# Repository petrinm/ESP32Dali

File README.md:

# ESP32Dali

ESP32Dali is an ESP32-based, [ESPHome](https://esphome.io/)-friendly interface to [DALI](https://en.wikipedia.org/wiki/Digital_Addressable_Lighting_Interface) lighting devices. It acts as a master on the DALI bus through an isolated front-end, and can also provide 18 V DALI supply voltage from 5 V input.

The board is a matchbox-sized 2-layer PCB that hosts an ESP32-WROOM-32 plus the DALI interface.

- Schematic & PCB: `hw/` ([KiCanvas](https://kicanvas.org/?github=https%3A%2F%2Fgithub.com%2Fpetrinm%2FESP32Dali%2Fblob%2Fmain%2Fhw%2FESPDali.kicad_sch), [PDF](https://github.com/petrinm/ESP32Dali/blob/main/hw/ESPDali.pdf))
- 3D STEP and printable enclosure: `3d/`
- ESPHome external components: `components/`

## Example ESPHome configuration

The `dali` component can be pulled in as an [external component](https://esphome.io/components/external_components), so the same configuration works on the ESP32Dali board and on any other ESP32 with a compatible DALI front-end.

```yaml
esphome:
  name: livingroom
  friendly_name: Livingroom

esp32:
  board: esp32dev
  framework:
    type: arduino

external_components:
  - source:
      type: git
      url: https://github.com/petrinm/ESP32Dali.git
    components: [ dali ]

dali:
  id: dali_if
  tx_pin:
    number: 17
    inverted: true
  rx_pin:
    number: 16
    inverted: true

light:
  # Dim-only gear on one short address:
  - platform: dali
    name: "LED strip"
    interface: dali_if
    address: 5
    default_transition_length: 1s   # converted to DALI fade time on the gear

# Dual DAPC CT (two DAPC channels, two short addresses):
# - platform: dali
#   name: "TW panel"
#   interface: dali_if
#   cold_white_address: 0
#   warm_white_address: 1
#   cold_white_color_temperature: 6536 K
#   warm_white_color_temperature: 2000 K

# DT8 CT on one address (DAPC + DT8 colour temperature command):
# - platform: dali
#   name: "DT8 lamp"
#   interface: dali_if
#   address: 5
#   cold_white_color_temperature: 6536 K
#   warm_white_color_temperature: 2000 K

# DT8 RGB on one address (SET TEMPORARY RGB DIM LEVEL + ACTIVATE):
# - platform: dali
#   name: "RGB strip"
#   interface: dali_if
#   address: 3
#   dt8_rgb: true

# Long sunrise (up to ~16 min uses DALI extended fade time on supported gear):
# - platform: dali
#   name: "Slow dim"
#   interface: dali_if
#   address: 5
#   default_transition_length: 15min
```

Build and flash with:

```bash
$ esphome run livingroom.yaml
```

## License

Released under the MIT License.

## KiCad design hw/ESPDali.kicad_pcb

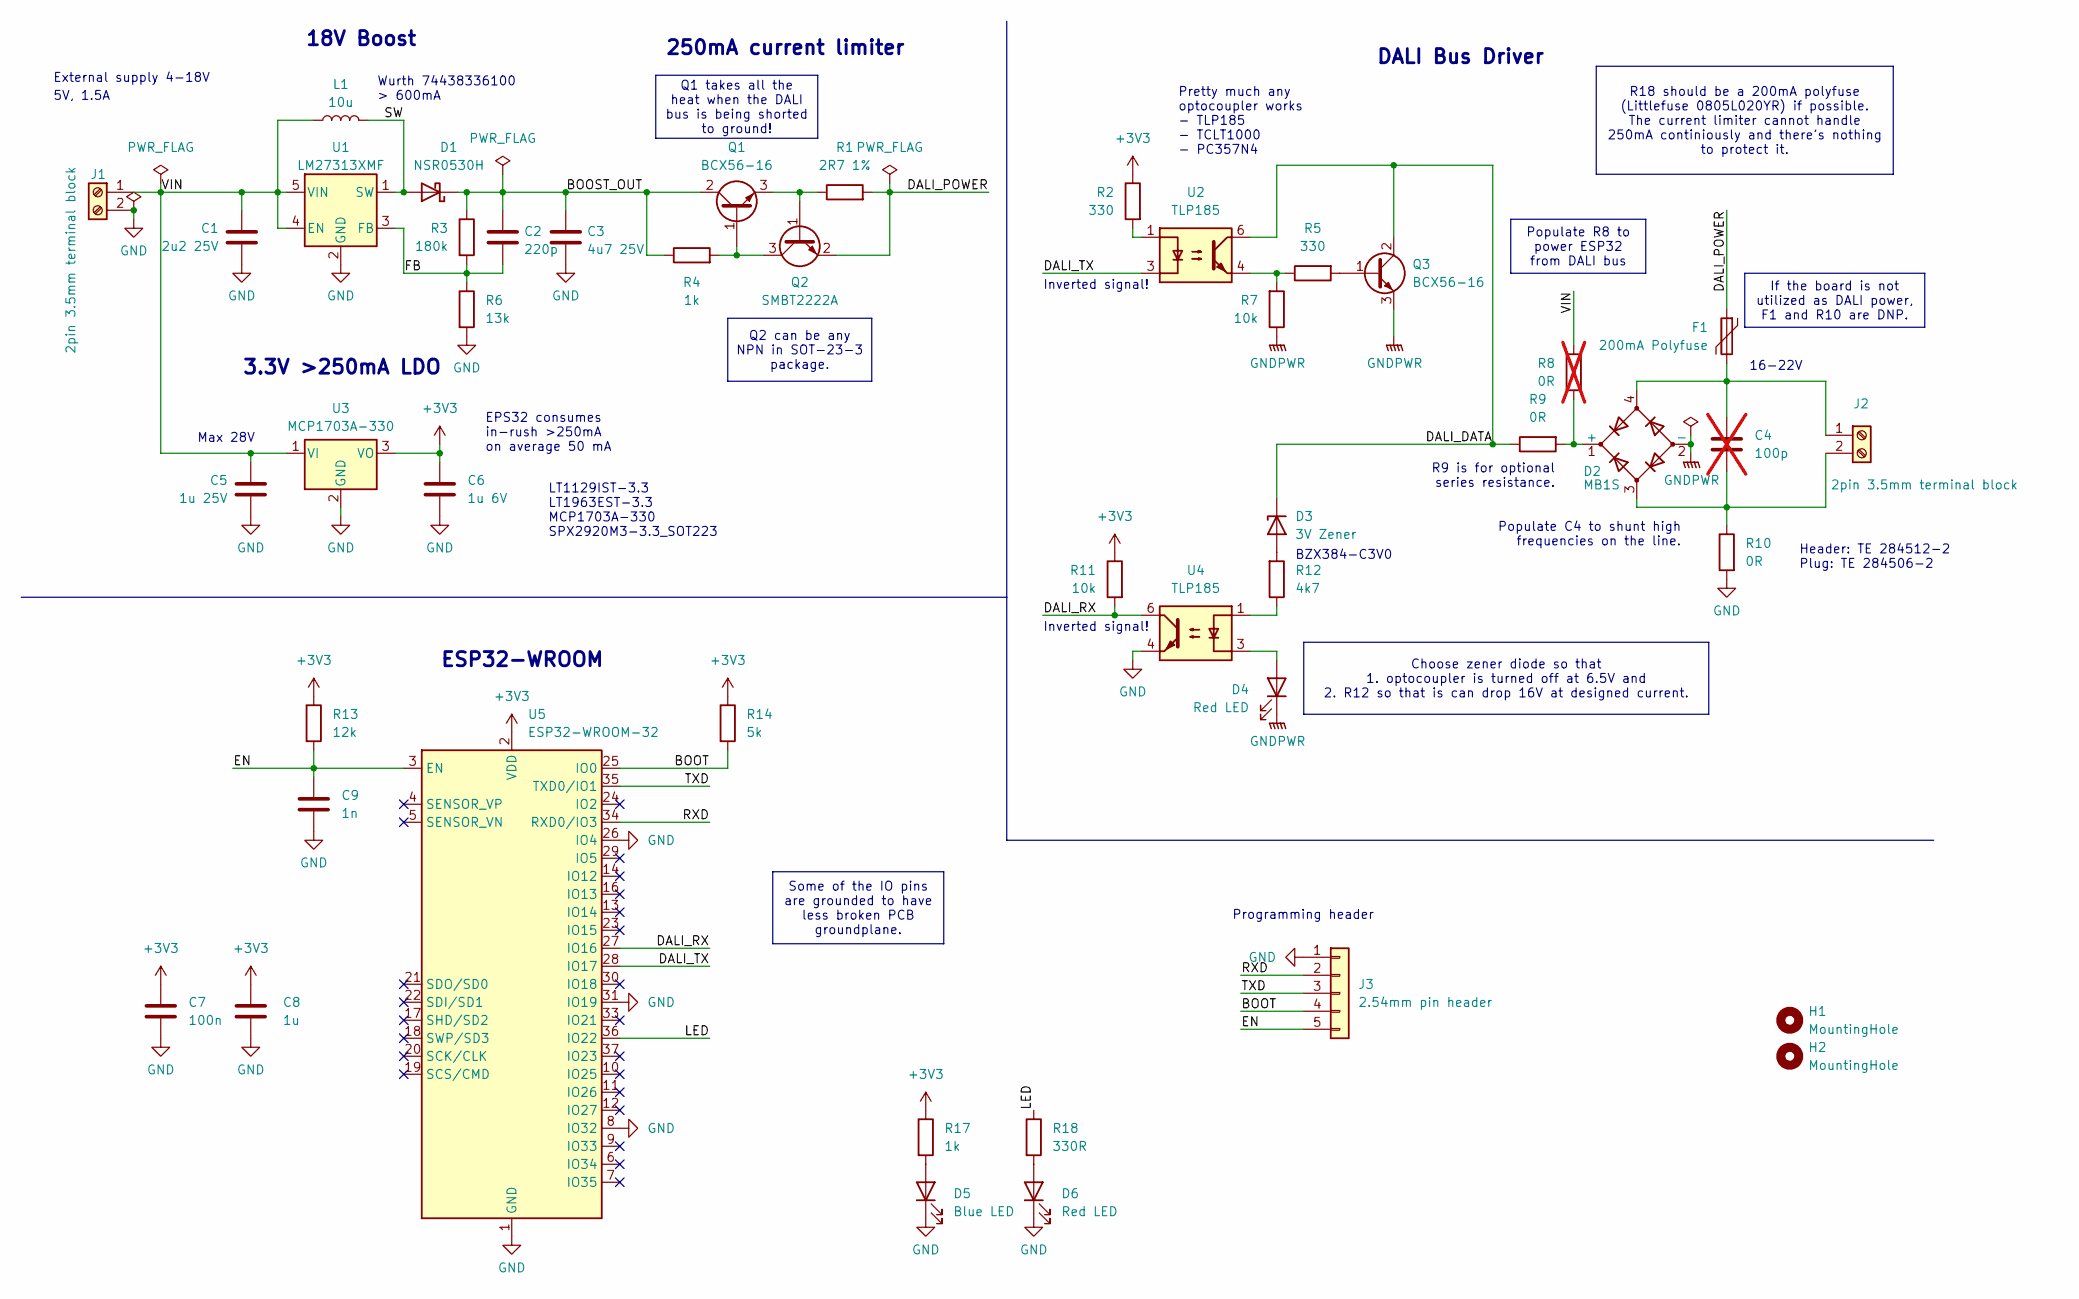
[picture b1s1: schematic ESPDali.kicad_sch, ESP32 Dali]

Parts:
C1: 2u2 25V; C_0805_2012Metric
C2: 220p; C_0603_1608Metric
C3: 4u7 25V; C_0805_2012Metric
C4: 100p; C_0603_1608Metric; not fitted
C5: 1u 25V; C_0805_2012Metric
C6: 1u 6V; C_0603_1608Metric
C7: 100n; C_0603_1608Metric
C8: 1u; C_0603_1608Metric
C9: 1n; C_0603_1608Metric
D1: NSR0530H; D_SOD-323
D2: MB1S
D3: 3V Zener; D_SOD-323
D4, D6: Red LED; LED_0603_1608Metric
D5: Blue LED; LED_0603_1608Metric
F1: 200mA Polyfuse; Fuse_0805_2012Metric
H1, H2: MountingHole; MountingHole_3.2mm_M3
J1, J2: 2pin 3.5mm terminal block; PhoenixContact_MC_1,5_2-G-3.5_1x02_P3.50mm_Horizontal
J3: 2.54mm pin header; PinHeader_1x05_P2.54mm_Vertical
L1: 10u; L_Wuerth_MAPI-3020
Q1, Q3: BCX56-16; SOT-89-3
Q2: SMBT2222A; SOT-23
R1: 2R7 1%; R_0805_2012Metric
R2, R5: 330; R_0603_1608Metric
R3: 180k; R_0603_1608Metric
R4, R17: 1k; R_0603_1608Metric
R6: 13k; R_0603_1608Metric
R7, R11: 10k; R_0603_1608Metric
R8: 0R; R_0805_2012Metric; not fitted
R9: 0R; R_0603_1608Metric
R10: 0R; R_0805_2012Metric
R12: 4k7; R_0603_1608Metric
R13: 12k; R_0603_1608Metric
R14: 5k; R_0603_1608Metric
R18: 330R; R_0603_1608Metric
U1: LM27313XMF; SOT-23-5
U2, U4: TLP185; SOIC-4_4.55x3.7mm_P2.54mm
U3: MCP1703A-330; SOT-223-3_TabPin2
U5: ESP32-WROOM-32

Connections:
+3V3: C6.1, C7.1, C8.1, R2.1, R11.1, R13.1, R14.1, R17.1, U3.3 (VO), U5.2 (VDD)
/BOOST_OUT: C2.1, C3.1, D1.1 (K), Q1.2 (C), R3.1, R4.1
/BOOT: J3.4, R14.2, U5.25 (IO0)
/DALI_DATA: D3.1 (K), Q3.2 (C), R9.1, U2.6
/DALI_POWER: F1.1, Q2.2 (E), R1.2
/DALI_RX: R11.2, U4.6, U5.27 (IO16)
/DALI_TX: U2.3, U5.28 (IO17)
/EN: C9.1, J3.5, R13.2, U5.3 (EN)
/FB: C2.2, R3.2, R6.1, U1.3 (FB)
/LED: R18.1, U5.36 (IO22)
/RXD: J3.2, U5.34 (RXD0/IO3)
/SW: D1.2 (A), L1.2, U1.1 (SW)
/TXD: J3.3, U5.35 (TXD0/IO1)
/VIN: C1.1, C5.1, J1.1, L1.1, R8.1, U1.4 (EN), U1.5 (VIN), U3.1 (VI)
GND: C1.2, C3.2, C5.2, C6.2, C7.2, C8.2, C9.2, D5.1 (K), D6.1 (K), J1.2, J3.1, R6.2, R10.2, U1.2 (GND), U3.2 (GND), U4.4, U5.1 (GND), U5.8 (IO32), U5.15 (GND), U5.26 (IO4), U5.31 (IO19), U5.38 (GND), U5.39 (GND)
GNDPWR: D2.2 (-), D4.1 (K), Q3.3 (E), R7.1
unnamed: D2.1 (+), R8.2, R9.2
unnamed: D3.2 (A), R12.2
unnamed: D4.2 (A), U4.3
unnamed: D5.2 (A), R17.2
unnamed: D6.2 (A), R18.2
unnamed: C4.1, D2.4, F1.2, J2.1
unnamed: C4.2, D2.3, J2.2, R10.1
unnamed: Q1.1 (B), Q2.3 (C), R4.2
unnamed: Q1.3 (E), Q2.1 (B), R1.1
unnamed: Q3.1 (B), R5.2
unnamed: R2.2, U2.1
unnamed: R5.1, R7.2, U2.4
unnamed: R12.1, U4.1

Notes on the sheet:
Q1 takes all the heat when the DALI bus is being shorted to ground!
Choose zener diode so that 1. optocoupler is turned off at 6.5V and 2. R12 so that is can drop 16V at designed current.
Q2 can be any NPN in SOT-23-3 package.
If the board is not utilized as DALI power, F1 and R10 are DNP.
Populate R8 to power ESP32 from DALI bus
R18 should be a 200mA polyfuse (Littlefuse 0805L020YR) if possible. The current limiter cannot handle 250mA continiously and there's nothing to protect it.
Some of the IO pins are grounded to have less broken PCB groundplane.
Pretty much any optocoupler works - TLP185 - TCLT1000 - PC357N4
ESP32-WROOM
16-22V
EPS32 consumes in-rush >250mA on average 50 mA
DALI Bus Driver
Populate C4 to shunt high frequencies on the line.
BZX384-C3V0
Wurth 74438336100 > 600mA
Inverted signal!
250mA current limiter
5V, 1.5A
Programming header
Max 28V
R9 is for optional series resistance.
3.3V >250mA LDO
External supply 4-18V
Header: TE 284512-2 Plug: TE 284506-2
18V Boost
LT1129IST-3.3 LT1963EST-3.3 MCP1703A-330 SPX2920M3-3.3_SOT223

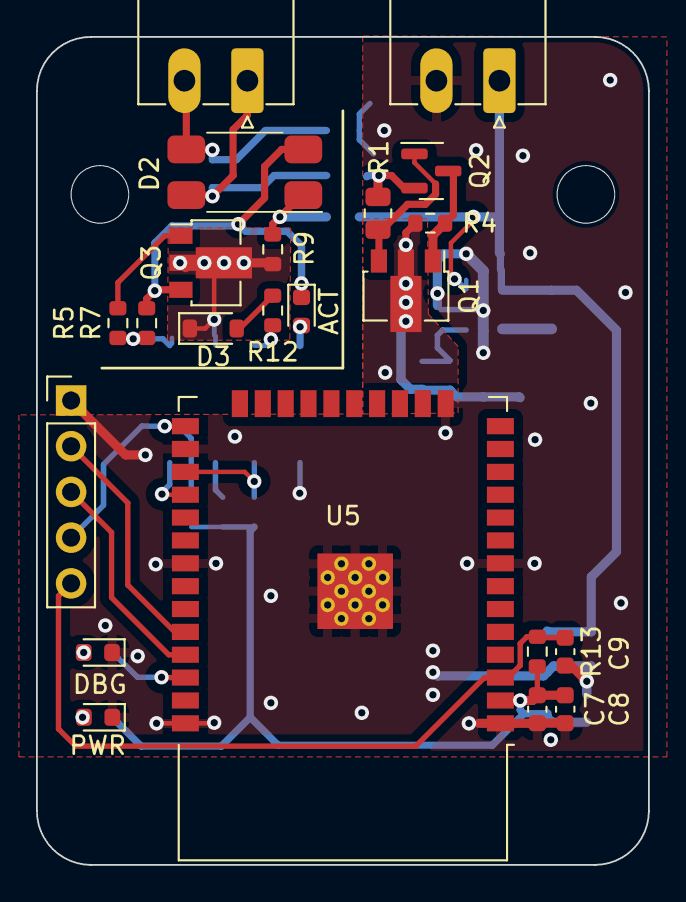
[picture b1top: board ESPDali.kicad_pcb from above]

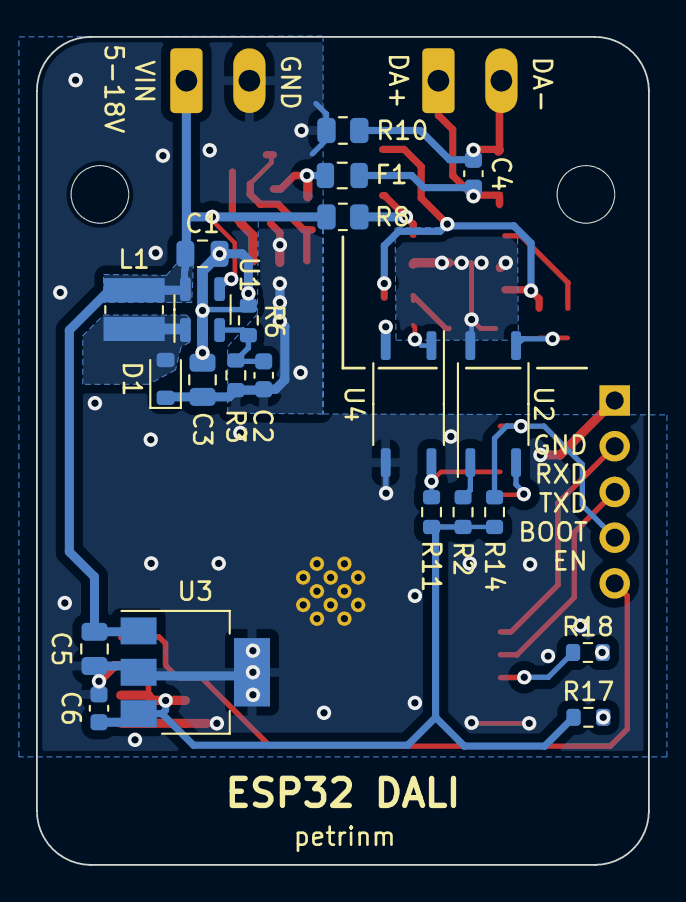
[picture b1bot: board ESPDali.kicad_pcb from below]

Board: 2 copper layers, 34.0 x 46.0 mm, 46 parts (22 on the bottom side), 29 nets.

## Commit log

2023-10-30 Add KiCAD temp files to .gitignore
2024-01-27 Add v1 KiCAD files
2024-02-16 Footprint fixes to PCB
2024-09-26 Update to KiCAD 8
2024-09-26 Add 3D files
2024-09-26 Add ibom
2024-09-26 Fix image url
2024-09-26 First version of the firmware
2024-10-14 Add more commands and other fixes
2026-05-18 Rework DALI driver
2026-05-18 Add Doxygen comments
2026-05-18 Use snake_case for variables
2026-05-18 Add DALILight platform, remove DALIOutput
2026-05-18 Add dual-channel tunable white to DALILight.
    Drive cold and warm channels on separate short addresses via DAPC, with YAML validation and README examples for dim, DT8, and dual-channel modes.
2026-05-18 Add DT8 RGB support and clarify CtMode names.
    Implement set_rgb() and DALILight dt8_rgb mode; rename DT8 to DT8_CT and DUAL_CHANNEL to DUAL_DAPC_CT.
2026-05-18 Map ESPHome transition duration to DALI fade configuration.
    Remove fadetime/faderate from DALILight YAML; add configure_fade_duration() with standard fade lookup table and extended fade for long ramps, plus gear-native transition transformer.
2026-05-18 Rename CtMode to ColorMode in DALILight.
    Rename ct_mode_ and set_ct_mode() to match the clearer ColorMode enum name.
2026-05-18 Add optional DALI identify and commissioning button platforms.
    Implement IEC 62386-102 discovery and short-address programming in the
    driver, with ESPHome buttons for IDENTIFY DEVICE and bus commissioning.
